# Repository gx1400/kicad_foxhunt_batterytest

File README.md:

# Fox Hunt Controller — Hardware Design

Custom amateur radio fox hunt (hidden transmitter) controller, aimed at being a flexible, dynamic platform for a wide range of fox-hunt formats — not just a fixed single-mode beacon. Built around an ESP32-S3, u-blox GPS module (MAX-M10S), and SA818S 2m RF module, with a WiFi/BLE web UI for configuration and "found" logging, RTOS-based scheduling, RTC-driven wake and precise TX timing, GPS-disciplined timekeeping, and APRS output capability. Firmware developed in PlatformIO. Boards fabricated and assembled via JLCPCB (including their SMT assembly service). Planned as an iterative multi-revision build, proving out core software before locking down hardware.

**Note:** this initial revision is a dev/learning board — built to test out the design, get hands-on with the parts and tooling, and work out mistakes before committing to a more polished revision.

## Contents

- [Setup](#setup)
- [Power architecture overview](#power-architecture-overview) (diagram — full detail in `_docs/`)
- **[Full docs index →](_docs/README.md)** — hardware design detail, controller/peripheral platform decisions, BOM sourcing/datasheets, open items

## Setup

All KiCad design files live under [`pcb/`](pcb/) — project file, schematics, PCB, and the vendored libraries. This project depends on three external symbol/footprint libraries, vendored as git submodules under `pcb/libs/` so the project is self-contained and doesn't require any machine-specific KiCad library setup. Project-level `sym-lib-table` and `fp-lib-table` files reference them via `${KIPRJMOD}`, so they resolve automatically once the submodules are checked out — no manual library registration needed.

Clone with submodules:

```sh
git clone --recurse-submodules https://github.com/gx1400/kicad_foxhunt_batterytest.git
```

The KiCad project file is at `pcb/foxhunt1.kicad_pro`.

Or, if already cloned:

```sh
git submodule update --init --recursive
```

Everything else (standard KiCad libraries: `Device`, `power`, `Resistor_SMD`, etc.) ships with any stock KiCad 10 install — no extra setup required.

## Power Architecture Overview

Two independent power sources feed the board, combined safely before regulation, then split into two independently-regulated rails:

```
18650 pack ──[MAX17320 protector]── +7.5V ──┐
                                              ├─[TPS2121 VCOMP]── VRAW ──[soft-latch FET]──┬─[Buck+LDO]── 5V  (SA818S)
12–14.5V input ──[fuse]── +12V ──────────────┘                                            └─[Buck+LDO]── 3.3V (ESP32-S3, GPS)
```

Full detail (battery protection, dual-input combining, regulation, the whole planned controller/peripheral platform, BOM sourcing, and open items) lives in **[`_docs/`](_docs/README.md)**.

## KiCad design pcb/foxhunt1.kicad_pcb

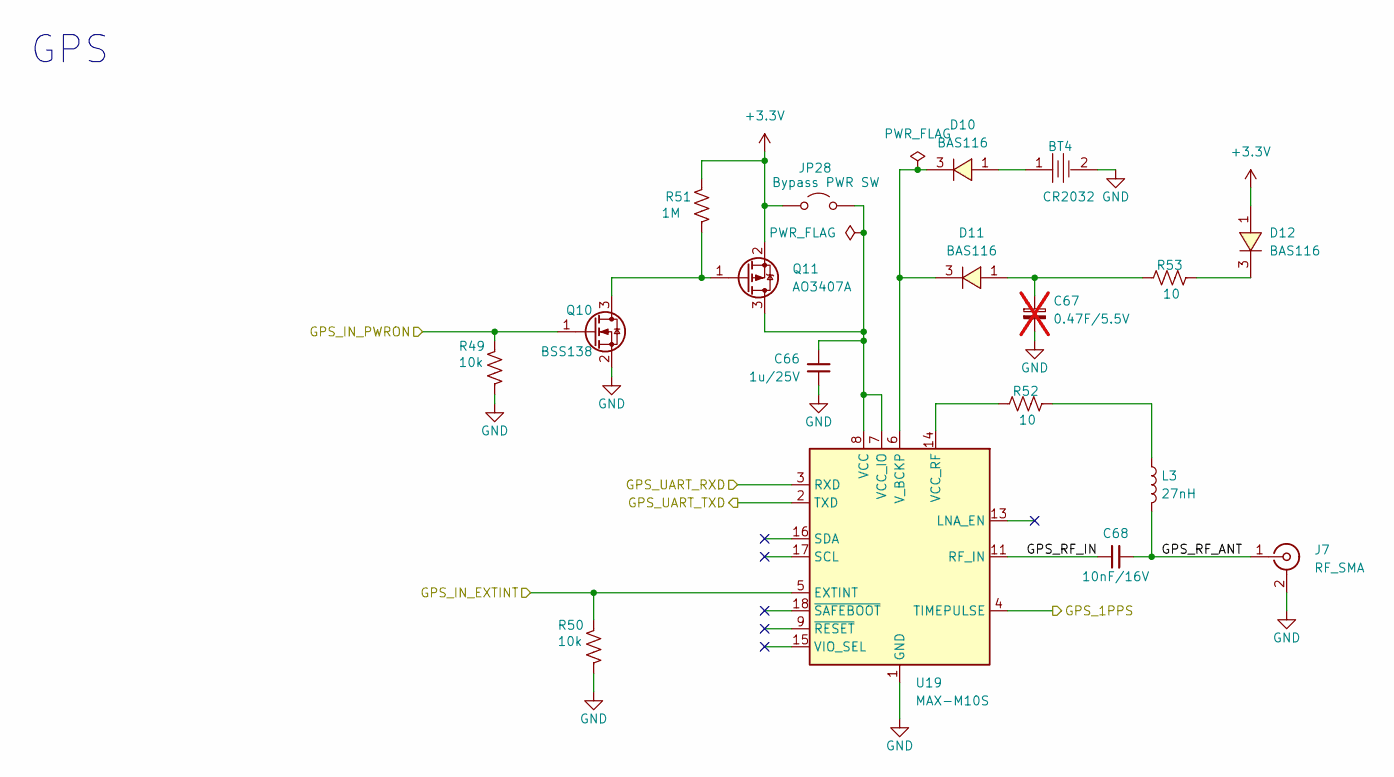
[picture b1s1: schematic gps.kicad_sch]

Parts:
BT4: CR2032; BAT-SMD_BS-08-B2AA016; MPN BS-08-B2AA020-R; LCSC Part C964787
C66: 1u/25V; C_0805_2012Metric; MPN GRM21BR71H105KA12L; LCSC Part # C77083
C67: 0.47F/5.5V; CP_Supercap_EDC474Z5R5V_0.2x5mm; MPN EDC474Z5R5V; LCSC Part # N/A; not fitted
C68: 10nF/16V; C_0603_1608Metric; MPN GRM188R71H103KA01D; LCSC Part # C77053
D10, D11, D12: BAS116; SOT-23_L2.9-W1.3-P1.90-LS2.4-BR; MPN BAS116LT1G; LCSC Part # C232527
J7: RF_SMA; SMA_Amphenol_132134-11_Vertical; MPN 132289; LCSC Part # C3172723
JP28: Bypass PWR SW; TestPoint_2Pads_Pitch2.54mm_Drill0.8mm
L3: 27nH; L_0402_1005Metric; MPN LQG15HS27NG02D; LCSC Part # C3910610
Q10: BSS138; SOT-23
Q11: AO3407A; SOT-23; MPN AO3407A; LCSC Part # C15155
R49, R50: 10k; R_0603_1608Metric; MPN RT0603BRD0710KL; LCSC Part # C95204
R51: 1M; R_0603_1608Metric; MPN RC0603FR-071ML; LCSC Part # C105578
R52: 10; R_1206_3216Metric; MPN RC1206FR-0710RL; LCSC Part # C108080
R53: 10; R_0603_1608Metric; MPN RC0603FR-0710RL; LCSC Part # C109318
U19: MAX-M10S; ublox_MAX; MPN MAX-M10S-00B; LCSC Part # C4153167

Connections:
+3.3V: D12.1, JP28.1 (A), Q11.2 (S), R51.2; also elsewhere on the board
/GPS/GPS_1PPS: U19.4 (TIMEPULSE); also elsewhere on the board
/GPS/GPS_IN_EXTINT: R50.2, U19.5 (EXTINT); also elsewhere on the board
/GPS/GPS_IN_PWRON: Q10.1 (G), R49.2; also elsewhere on the board
/GPS/GPS_RF_ANT: C68.2, J7.1 (In), L3.2
/GPS/GPS_RF_IN: C68.1, U19.11 (RF_IN)
/GPS/GPS_UART_RXD: U19.3 (RXD); also elsewhere on the board
/GPS/GPS_UART_TXD: U19.2 (TXD); also elsewhere on the board
GND: BT4.2, C66.2, C67.2, J7.2 (Ext), Q10.2 (S), R49.1, R50.1, U19.1 (GND), U19.10 (GND), U19.12 (GND); also elsewhere on the board
unnamed: BT4.1, D10.1
unnamed: C67.1, D11.1, R53.2
unnamed: D12.3, R53.1
unnamed: C66.1, JP28.2 (B), Q11.3 (D), U19.7 (VCC_IO), U19.8 (VCC)
unnamed: L3.1, R52.1
unnamed: Q10.3 (D), Q11.1 (G), R51.1
unnamed: R52.2, U19.14 (VCC_RF)
unnamed: D10.3, D11.3, U19.6 (V_BCKP)

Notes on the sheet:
GPS

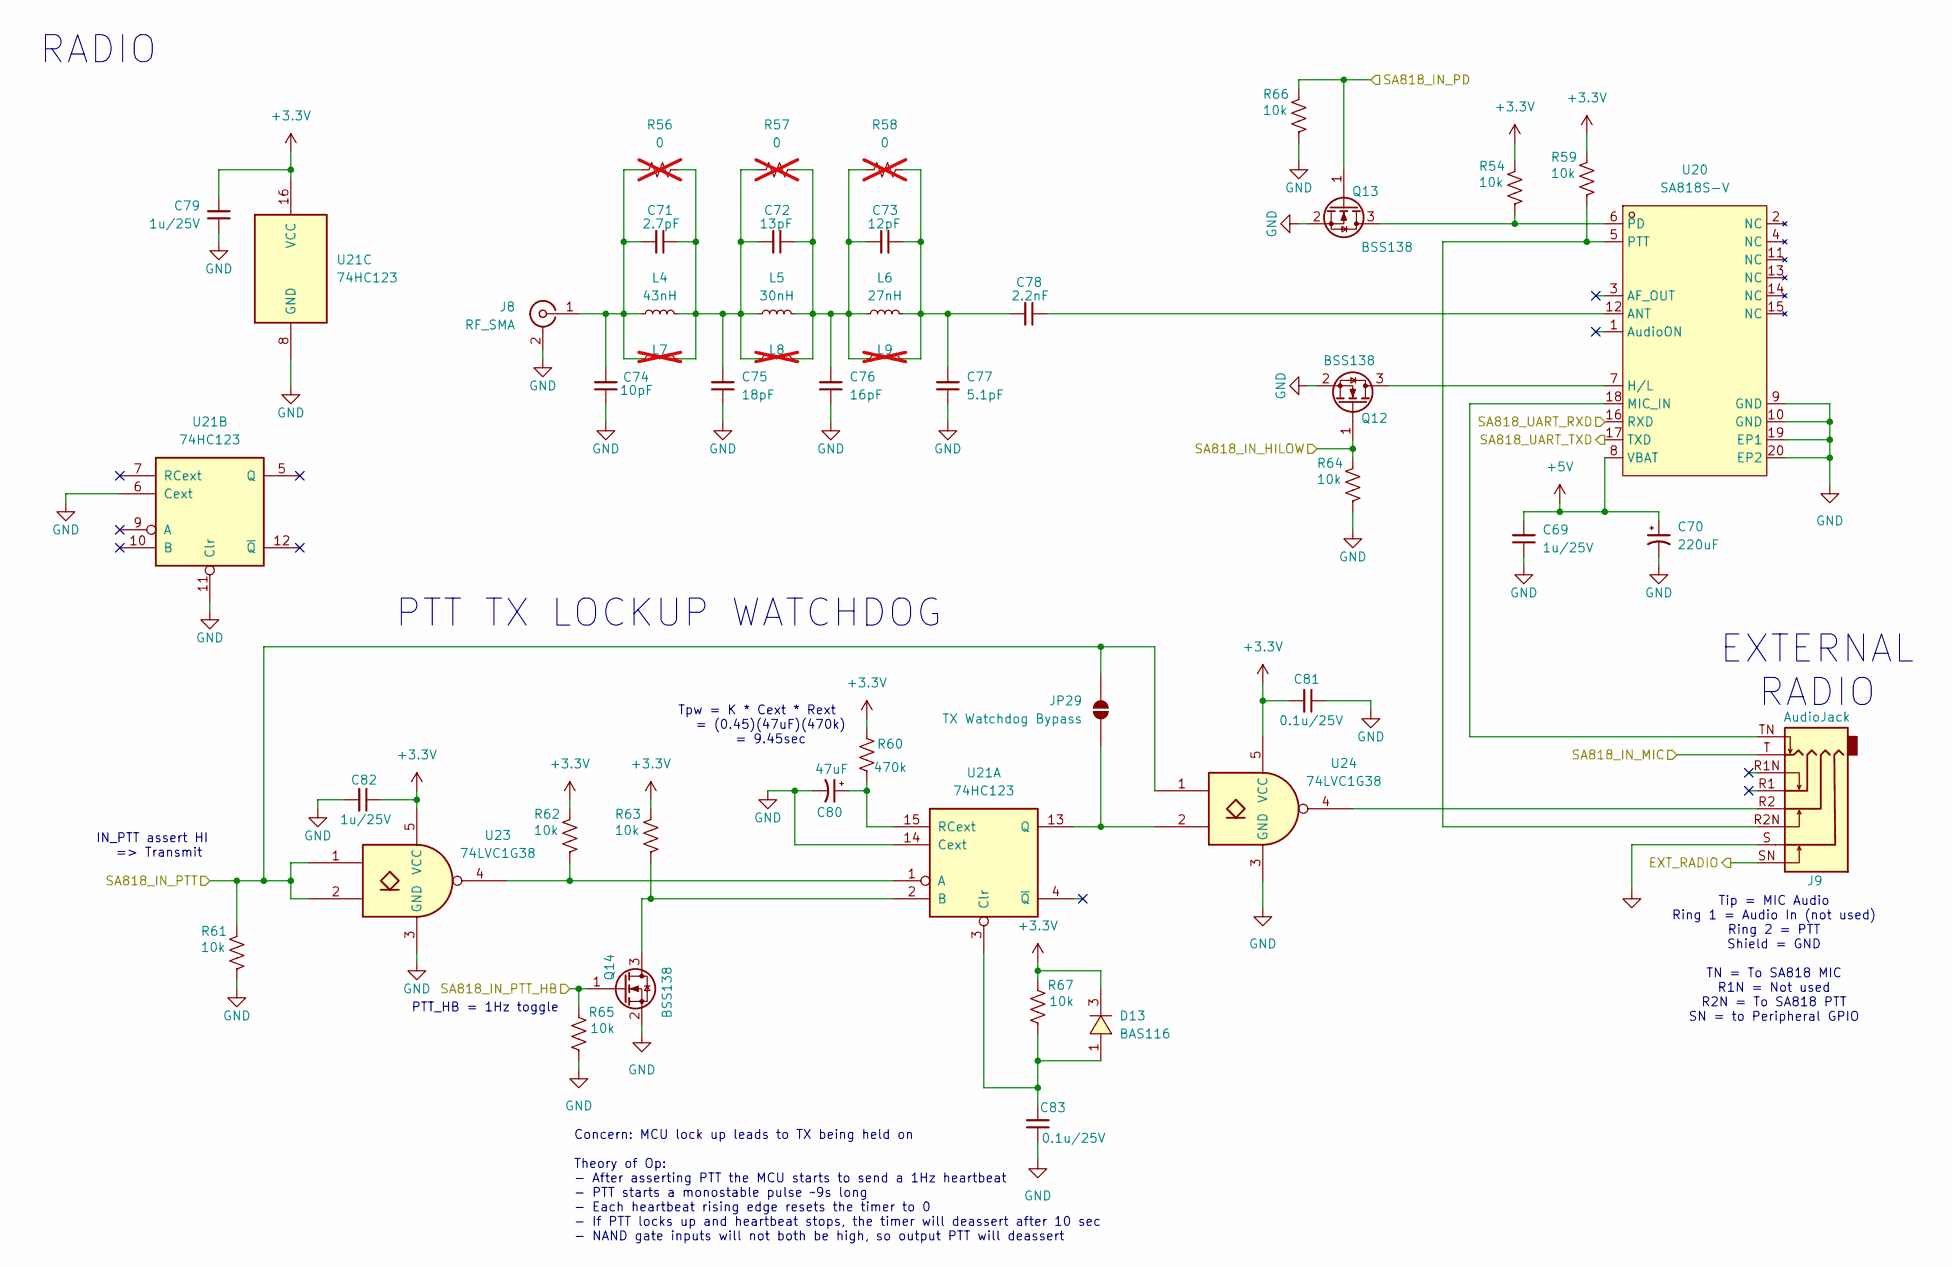
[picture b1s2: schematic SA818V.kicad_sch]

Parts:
C69, C79, C82: 1u/25V; C_0805_2012Metric; MPN GRM21BR71H105KA12L; LCSC Part # C77083
C70: 220uF; CP_Elec_6.3x7.7; MPN DMBJ; LCSC Part # C970695
C71: 2.7pF; C_0603_1608Metric_Pad1.08x0.95mm_HandSolder; MPN GRM1885C1H2R7BA01D; LCSC Part # C162221
C72: 13pF; C_0201_0603Metric_Pad0.64x0.40mm_HandSolder; MPN 0603CG130J500NT; LCSC Part # C34243
C73: 12pF; C_0603_1608Metric_Pad1.08x0.95mm_HandSolder; MPN 0603CG120J500NT; LCSC Part # C1642
C74: 10pF; C_0603_1608Metric_Pad1.08x0.95mm_HandSolder; MPN GRM1885C1H100JA01D; LCSC Part # C84498
C75: 18pF; C_0603_1608Metric_Pad1.08x0.95mm_HandSolder; MPN 0603CG180J500NT; LCSC Part # C92671
C76: 16pF; C_0603_1608Metric_Pad1.08x0.95mm_HandSolder; MPN 0603CG160J500NT; LCSC Part # C1646
C77: 5.1pF; C_0603_1608Metric_Pad1.08x0.95mm_HandSolder; MPN GRM1885C1H5R1CA01D; LCSC Part # C6955114
C78: 2.2nF; C_0603_1608Metric_Pad1.08x0.95mm_HandSolder; MPN GRM1885C1H222JA01J; LCSC Part # C2168957
C80: 47uF; CP-SMD_1206_L3.2-W1.6-FD; MPN TMCMA1A476MTRF; LCSC Part # C4984790
C81, C83: 0.1u/25V; C_0603_1608Metric; MPN GRM188R71H104KA93D; LCSC Part # C77055
D13: BAS116; SOT-23_L2.9-W1.3-P1.90-LS2.4-BR; MPN BAS116LT1G; LCSC Part # C232527
J8: RF_SMA; SMA_Amphenol_132134-11_Vertical; MPN 132289; LCSC Part # C3172723
J9: AudioJack; Jack_SJ-43617-SMT-TR; MPN SJ-43617-SMT-TR; Digikey CP-43617SJTR-ND
JP29: TX Watchdog Bypass; SolderJumper-2_P1.3mm_Open_TrianglePad1.0x1.5mm
L4: 43nH; L_0805_2012Metric_Pad1.05x1.20mm_HandSolder; MPN LQW2BAN43NG00L; LCSC Part # C1330253
L5: 30nH; L_0805_2012Metric_Pad1.05x1.20mm_HandSolder; MPN LQW2BAN30NG00L; LCSC Part # C3221803
L6: 27nH; L_0805_2012Metric_Pad1.05x1.20mm_HandSolder; MPN LQW2BAN27NJ00L; LCSC Part # C1330812
L7, L8, L9: L_0603_1608Metric; not fitted
Q12, Q13, Q14: BSS138; SOT-23
R54, R59, R61, R62, R63, R64, R65, R66, R67: 10k; R_0603_1608Metric; MPN RT0603BRD0710KL; LCSC Part # C95204
R56, R57, R58: 0; R_0603_1608Metric; MPN RC0603JR-070RL; LCSC Part # C95177; not fitted
R60: 470k; R_0603_1608Metric; MPN RC0603FR-07470KL; LCSC Part # C114622
U20: SA818S-V; WIRELM-SMD_G-NICERF_SA818S-X; MPN SA818S-V; LCSC Part C51897911
U21: 74HC123; SOIC-16_3.9x9.9mm_P1.27mm; MPN 74HC123D,653; LCSC Part # C5597
U23, U24: 74LVC1G38; SOT-23-5; MPN SN74LVC1G38DBVR; LCSC Part # C2867613

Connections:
+3.3V: C79.1, C81.1, C82.1, D13.3, R54.2, R59.2, R60.1, R62.2, R63.2, R67.2, U21.16 (VCC), U23.5 (VCC), U24.5 (VCC); also elsewhere on the board
+5V: C69.1, C70.1, U20.8 (VBAT); also elsewhere on the board
/Audio/I2S_MIC_OUT: J9.T; also elsewhere on the board
/Peripherals/PERIPH_OUT_SA818_HILOW: Q12.1 (G), R64.2; also elsewhere on the board
/Peripherals/PERIPH_OUT_SA818_PD: Q13.1 (G), R66.2; also elsewhere on the board
/SA818S-V/EXT_RADIO: J9.SN; also elsewhere on the board
/SA818S-V/SA818_IN_PTT: JP29.2 (B), R61.2, U23.1, U23.2, U24.1; also elsewhere on the board
/SA818S-V/SA818_IN_PTT_HB: Q14.1 (G), R65.2; also elsewhere on the board
/SA818S-V/SA818_UART_RXD: U20.16 (RXD); also elsewhere on the board
/SA818S-V/SA818_UART_TXD: U20.17 (TXD); also elsewhere on the board
GND: C69.2, C70.2, C74.1, C75.1, C76.1, C77.1, C79.2, C80.2, C81.2, C82.2, C83.1, J8.2 (Ext), J9.S, Q12.2 (S), Q13.2 (S), Q14.2 (S), R61.1, R64.1, R65.1, R66.1, U20.9 (GND), U20.10 (GND), U20.19 (EP1), U20.20 (EP2), U21.6 (Cext), U21.8 (GND), U21.11 (Clr), U21.14 (Cext), U23.3 (GND), U24.3 (GND); also elsewhere on the board
unnamed: C71.2, C72.1, C75.2, L4.2, L5.1, L7.2, L8.1, R56.2, R57.1
unnamed: C72.2, C73.1, C76.2, L5.2, L6.1, L8.2, L9.1, R57.2, R58.1
unnamed: C73.2, C77.2, C78.1, L6.2, L9.2, R58.2
unnamed: C71.1, C74.2, J8.1 (In), L4.1, L7.1, R56.1
unnamed: J9.R2, U24.4
unnamed: JP29.1 (A), U21.13 (Q), U24.2
unnamed: Q12.3 (D), U20.7 (H/L)
unnamed: Q13.3 (D), R54.1, U20.6 (PD)
unnamed: Q14.3 (D), R63.1, U21.2 (B)
unnamed: C78.2, U20.12 (ANT)
unnamed: J9.TN, U20.18 (MIC_IN)
unnamed: J9.R2N, R59.1, U20.5 (PTT)
unnamed: R62.1, U21.1 (A), U23.4
unnamed: C83.2, D13.1, R67.1, U21.3 (Clr)
unnamed: C80.1, R60.2, U21.15 (RCext)

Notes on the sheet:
IN_PTT assert HI => Transmit
Tip = MIC Audio Ring 1 = Audio In (not used) Ring 2 = PTT Shield = GND TN = To SA818 MIC R1N = Not used R2N = To SA818 PTT SN = to Peripheral GPIO
EXTERNAL RADIO
Tpw = K * Cext * Rext = (0.45)(47uF)(470k) = 9.45sec
PTT_HB = 1Hz toggle
RADIO
PTT TX LOCKUP WATCHDOG
Concern: MCU lock up leads to TX being held on Theory of Op: - After asserting PTT the MCU starts to send a 1Hz heartbeat - PTT starts a monostable pulse ~9s long - Each heartbeat rising edge resets the timer to 0 - If PTT locks up and heartbeat stops, the timer will deassert after 10 sec - NAND ga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

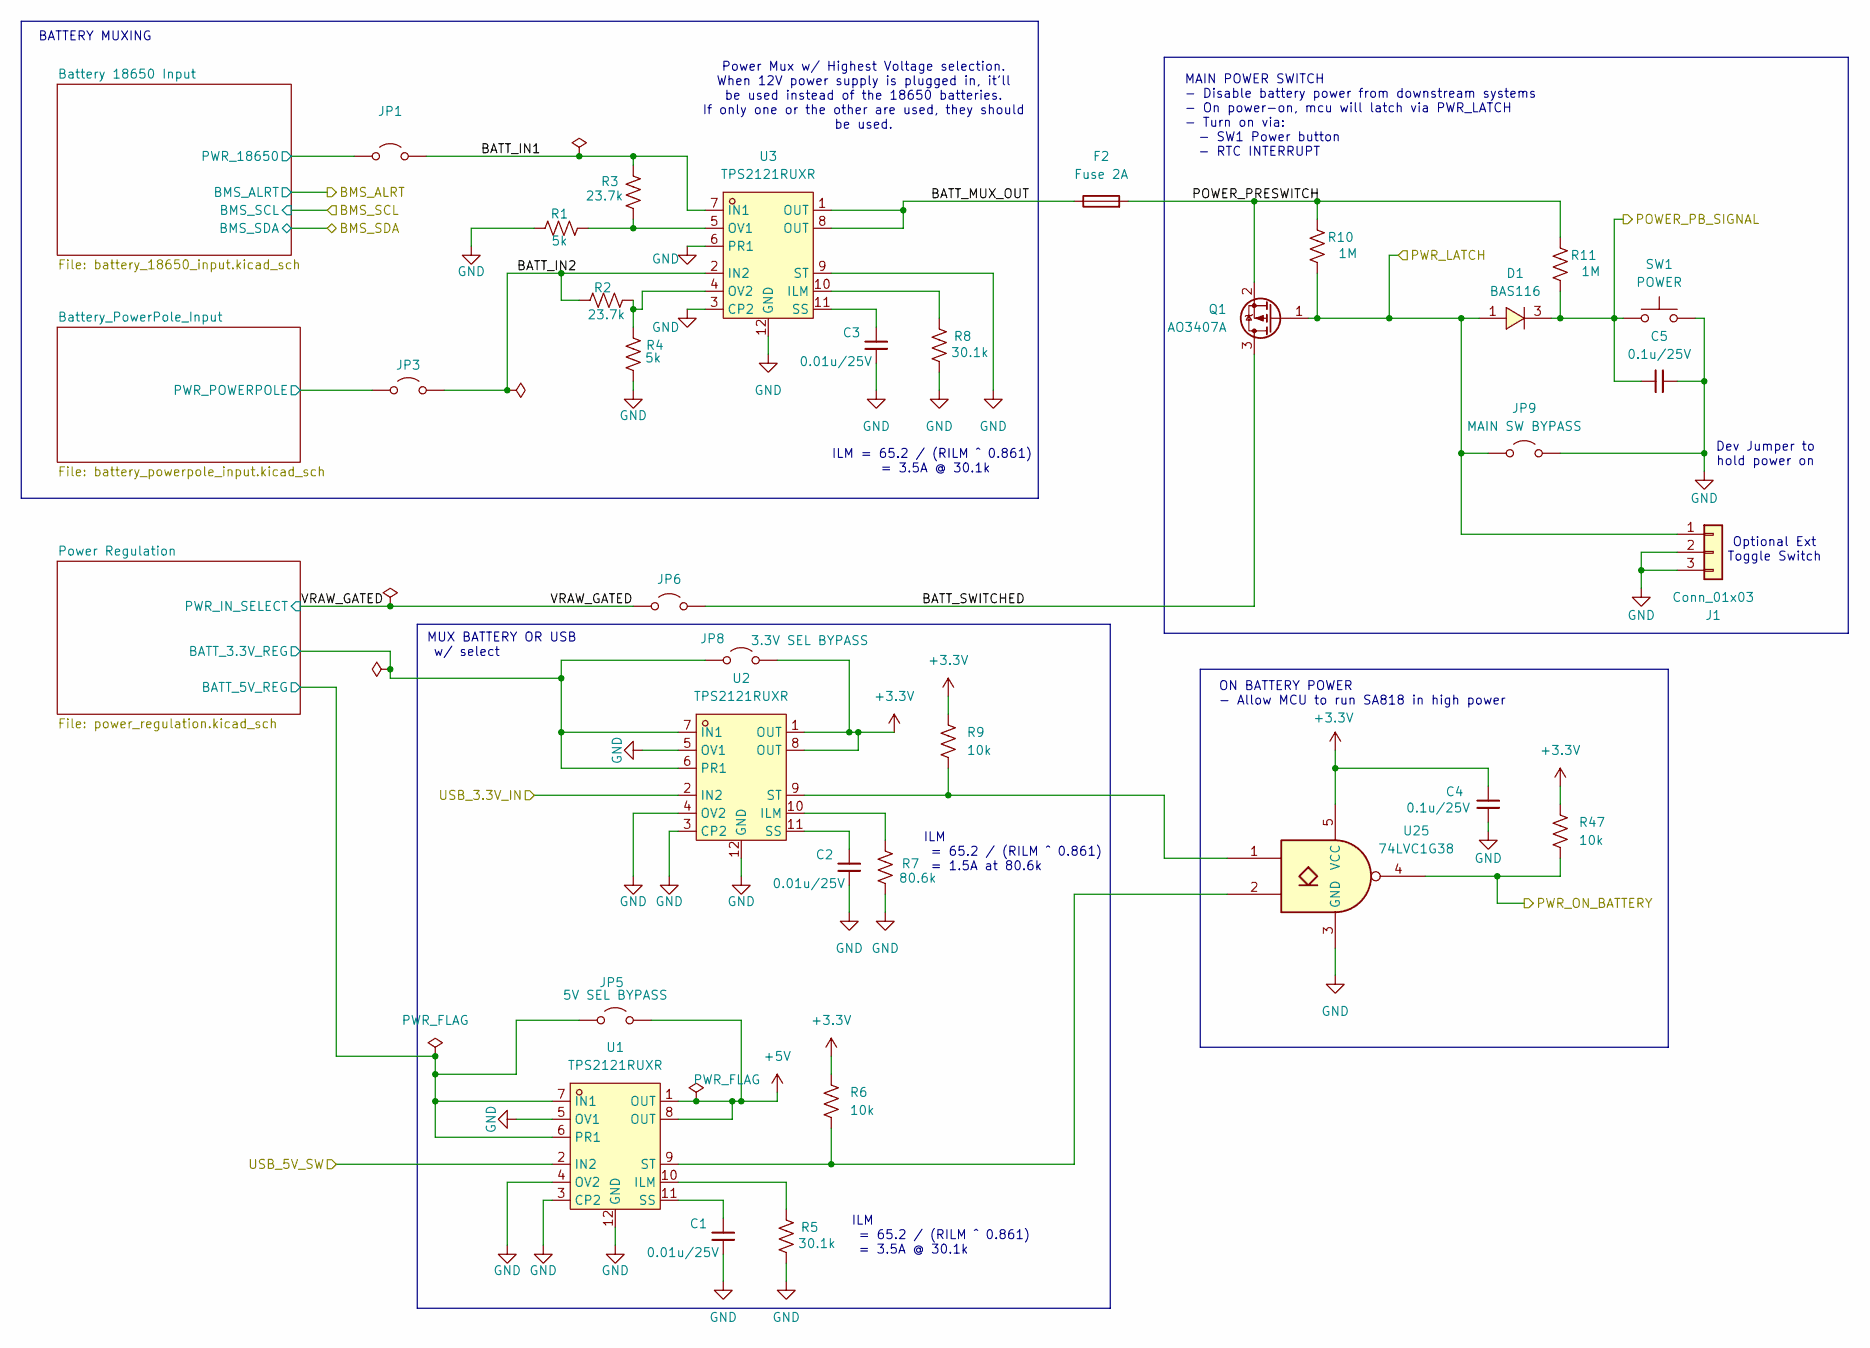
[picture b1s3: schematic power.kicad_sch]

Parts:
C1, C2, C3: 0.01u/25V; C_0603_1608Metric; MPN GRM1885C1H103JA01D; LCSC Part # C85973
C4, C5: 0.1u/25V; C_0603_1608Metric; MPN GRM188R71H104KA93D; LCSC Part # C77055
D1: BAS116; SOT-23_L2.9-W1.3-P1.90-LS2.4-BR; MPN BAS116LT1G; LCSC Part # C232527
F2: Fuse 2A; Fuse_MCCQ-122; MPN MCCQ-122
J1: Conn_01x03; JST_PH_B3B-PH-SM4-TB_1x03-1MP_P2.00mm_Vertical; MPN B3B-PH-SM4-TB(LF)(SN); LCSC Part # C160353
JP1: BATT IN ISO; TestPoint_2Pads_Pitch2.54mm_Drill0.8mm
JP3: 12V IN ISO; TestPoint_2Pads_Pitch2.54mm_Drill0.8mm
JP5: 5V SEL BYPASS; TestPoint_2Pads_Pitch2.54mm_Drill0.8mm
JP6: PWR ISO; TestPoint_2Pads_Pitch2.54mm_Drill0.8mm
JP8: 3.3V SEL BYPASS; TestPoint_2Pads_Pitch2.54mm_Drill0.8mm
JP9: MAIN SW BYPASS; TestPoint_2Pads_Pitch2.54mm_Drill0.8mm
Q1: AO3407A; SOT-23; MPN AO3407A; LCSC Part # C15155
R1, R4: 5k; R_0201_0603Metric; MPN RT0603BRE075KL; LCSC Part # C862232
R2, R3: 23.7k; R_0603_1608Metric; MPN 0603WAF2372T5E; LCSC Part # C22912
R5, R8: 30.1k; R_0603_1608Metric; MPN RC0603FR-0730K1L; LCSC Part # C137745
R6, R9, R47: 10k; R_0603_1608Metric; MPN RT0603BRD0710KL; LCSC Part # C95204
R7: 80.6k; R_0603_1608Metric; MPN RT0603BRE0780K6L; LCSC Part # C862291
R10: 1M; R_0603_1608Metric; MPN RC0603FR-071ML; LCSC Part # C105578
R11: 1M; R_0603_1608Metric; MPN RC0603JR-071ML; LCSC Part # C107698
SW1: POWER; SW_SPST_PTS645Sx43SMTR92; MPN K2-1102SP-A4SC-04; LCSC Part # C83916
U1, U2, U3: TPS2121RUXR; VQFN-HR-12_L2.5-W2.0-P0.50-BL; MPN TPS2121RUXR; LCSC Part # C485916
U25: 74LVC1G38; SOT-23-5; MPN SN74LVC1G38DBVR; LCSC Part # C2867613

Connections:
+3.3V: C4.1, JP8.2 (B), R6.2, R9.2, R47.2, U2.1 (OUT), U2.8 (OUT), U25.5 (VCC); also elsewhere on the board
+5V: JP5.2 (B), U1.1 (OUT), U1.8 (OUT); also elsewhere on the board
/Peripherals/RTC_OUT_INTERRUPT_LATCH: D1.1, J1.1, JP9.1 (A), Q1.1 (G), R10.1; also elsewhere on the board
/Power/BATT_IN1: JP1.2 (B), R3.2, U3.7 (IN1)
/Power/BATT_IN2: JP3.2 (B), R2.2, U3.2 (IN2)
/Power/BATT_MUX_OUT: F2.1, U3.1 (OUT), U3.8 (OUT)
/Power/BATT_SWITCHED: JP6.2 (B), Q1.3 (D)
/Power/Battery 18650 Input/PWR_18650: JP1.1 (A); also elsewhere on the board
/Power/Battery_PowerPole_Input/PWR_POWERPOLE: JP3.1 (A); also elsewhere on the board
/Power/POWER_PB_SIGNAL: C5.1, D1.3, R11.1, SW1.2; also elsewhere on the board
/Power/POWER_PRESWITCH: F2.2, Q1.2 (S), R10.2, R11.2
/Power/PWR_ON_BATTERY: R47.1, U25.4; also elsewhere on the board
/Power/Power Regulation/BATT_3.3V_REG: JP8.1 (A), U2.6 (PR1), U2.7 (IN1); also elsewhere on the board
/Power/Power Regulation/BATT_5V_REG: JP5.1 (A), U1.6 (PR1), U1.7 (IN1); also elsewhere on the board
/Power/USB_3.3V_IN: U2.2 (IN2); also elsewhere on the board
/Power/USB_5V_SW: U1.2 (IN2); also elsewhere on the board
/Power/VRAW_GATED: JP6.1 (A); also elsewhere on the board
GND: C1.2, C2.2, C3.2, C4.2, C5.2, J1.2, J1.3, JP9.2 (B), R1.1, R4.1, R5.1, R7.1, R8.1, SW1.1, U1.3 (CP2), U1.4 (OV2), U1.5 (OV1), U1.12 (GND), U2.3 (CP2), U2.4 (OV2), U2.5 (OV1), U2.12 (GND), U3.3 (CP2), U3.6 (PR1), U3.9 (ST), U3.12 (GND), U25.3 (GND); also elsewhere on the board
unnamed: R5.2, U1.10 (ILM)
unnamed: C1.1, U1.11 (SS)
unnamed: R6.1, U1.9 (ST), U25.2
unnamed: R7.2, U2.10 (ILM)
unnamed: C2.1, U2.11 (SS)
unnamed: R9.1, U2.9 (ST), U25.1
unnamed: R8.2, U3.10 (ILM)
unnamed: R1.2, R3.1, U3.5 (OV1)
unnamed: R2.1, R4.2, U3.4 (OV2)
unnamed: C3.1, U3.11 (SS)

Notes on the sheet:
ILM = 65.2 / (RILM ^ 0.861) = 1.5A at 80.6k
Optional Ext Toggle Switch
Dev Jumper to hold power on
Power Mux w/ Highest Voltage selection. When 12V power supply is plugged in, it'll be used instead of the 18650 batteries. If only one or the other are used, they should be used.
ON BATTERY POWER - Allow MCU to run SA818 in high power
ILM = 65.2 / (RILM ^ 0.861) = 3.5A @ 30.1k
MUX BATTERY OR USB w/ select
ILM = 65.2 / (RILM ^ 0.861) = 3.5A @ 30.1k
BATTERY MUXING
MAIN POWER SWITCH - Disable battery power from downstream systems - On power-on, mcu will latch via PWR_LATCH - Turn on via: - SW1 Power button - RTC INTERRUPT

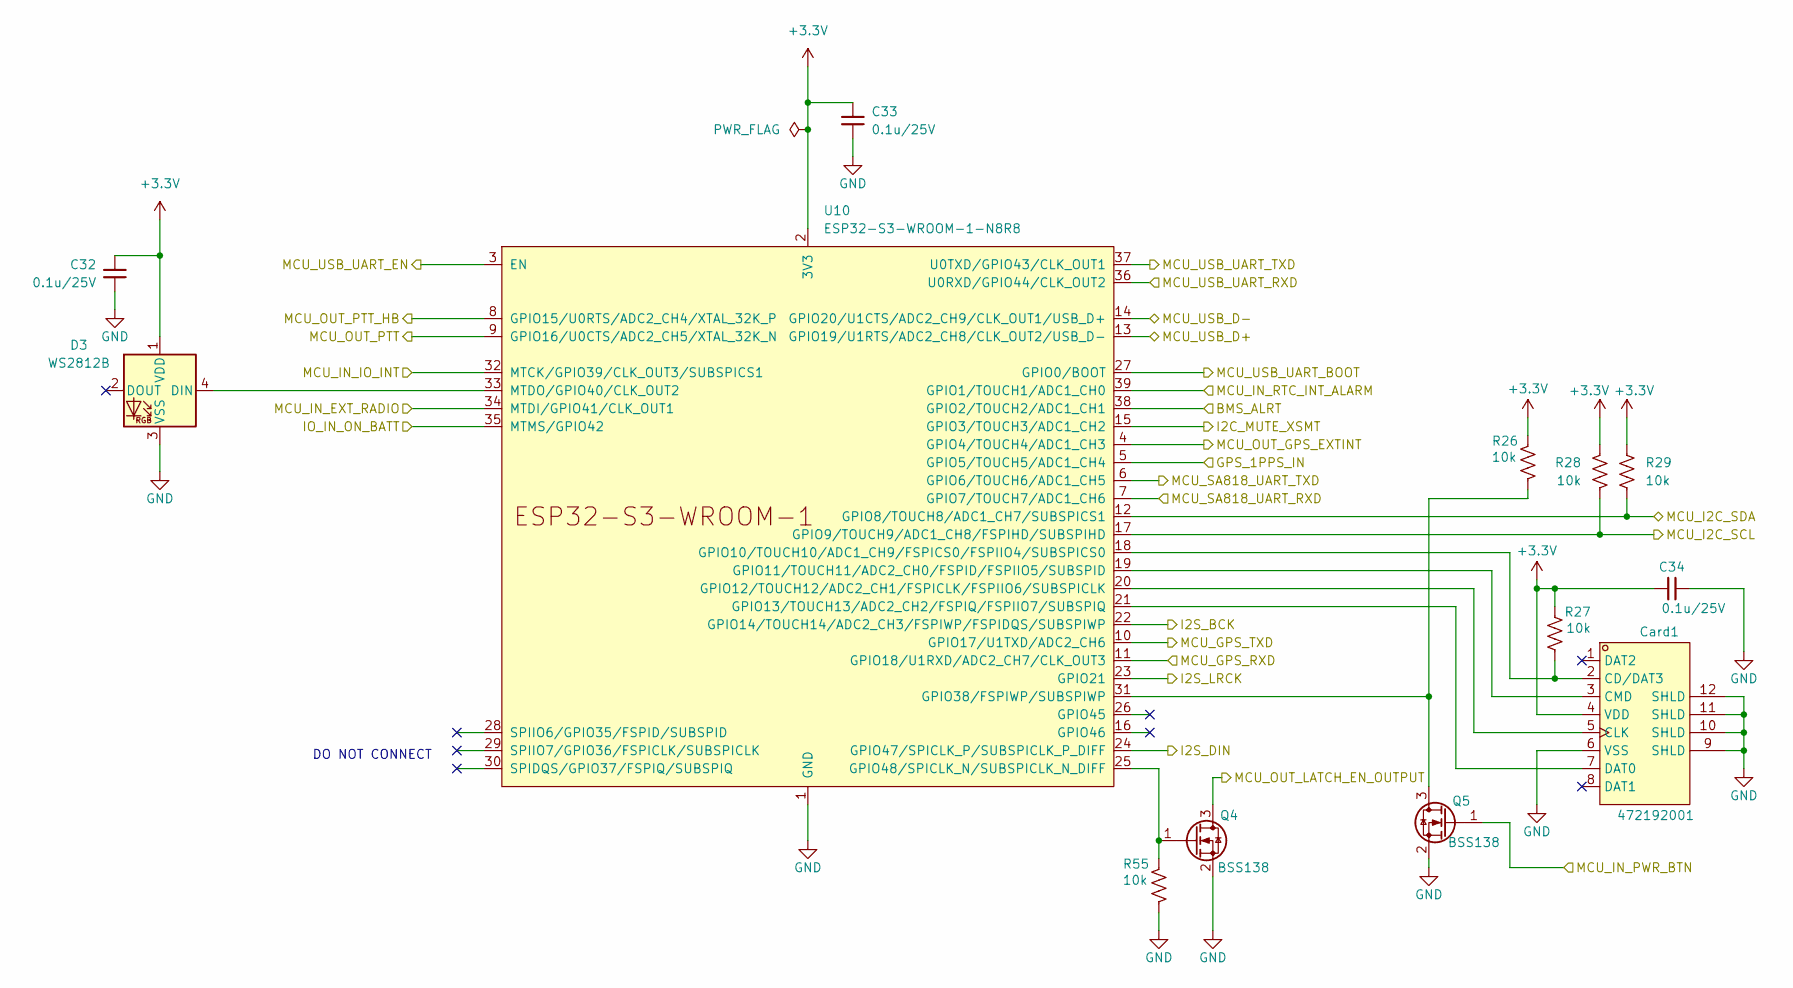
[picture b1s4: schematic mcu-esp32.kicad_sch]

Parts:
C32, C33, C34: 0.1u/25V; C_0603_1608Metric; MPN GRM188R71H104KA93D; LCSC Part # C77055
Card1: 472192001; TF-SMD_472192001; MPN 472192001; LCSC Part # C164170
D3: WS2812B; LED_WS2812B_PLCC4_5.0x5.0mm_P3.2mm; MPN WS2812B-B/W; LCSC Part # C114586
Q4, Q5: BSS138; SOT-23
R26, R27, R28, R29, R55: 10k; R_0603_1608Metric; MPN RT0603BRD0710KL; LCSC Part # C95204
U10: ESP32-S3-WROOM-1-N8R8; ESP32-S3-WROOM-1; MPN ESP32-S3-WROOM-1-N8R8; LCSC Part # C2913201

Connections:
+3.3V: C32.1, C33.1, C34.1, Card1.4 (VDD), D3.1 (VDD), R26.2, R27.2, R28.2, R29.2, U10.2 (3V3); also elsewhere on the board
/Audio/I2S_BCK: U10.22 (GPIO14/TOUCH14/ADC2_CH3/FSPIWP/FSPIDQS/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); also elsewhere on the board
/Audio/I2S_DIN: U10.24 (GPIO47/SPICLK_P/SUBSPICLK_P_DIFF); also elsewhere on the board
/Audio/I2S_LRCK: U10.23 (GPIO21); also elsewhere on the board
/Audio/I2S_XSMT: U10.15 (GPIO3/TOUCH3/ADC1_CH2); also elsewhere on the board
/GPS/GPS_1PPS: U10.5 (GPIO5/TOUCH5/ADC1_CH4); also elsewhere on the board
/GPS/GPS_IN_EXTINT: U10.4 (GPIO4/TOUCH4/ADC1_CH3); also elsewhere on the board
/GPS/GPS_UART_RXD: U10.10 (GPIO17/U1TXD/ADC2_CH6); also elsewhere on the board
/GPS/GPS_UART_TXD: U10.11 (GPIO18/U1RXD/ADC2_CH7/CLK_OUT3); also elsewhere on the board
/Peripherals/PERIPH_IO_INT: U10.32 (MTCK/GPIO39/CLK_OUT3/SUBSPICS1); also elsewhere on the board
/Peripherals/PERIPH_SCL: R28.1, U10.17 (GPIO9/TOUCH9/ADC1_CH8/FSPIHD/SUBSPIHD); also elsewhere on the board
/Peripherals/PERIPH_SDA: R29.1, U10.12 (GPIO8/TOUCH8/ADC1_CH7/SUBSPICS1); also elsewhere on the board
/Peripherals/RTC_OUT_INTERRUPT_LATCH: Q4.3 (D); also elsewhere on the board
/Peripherals/RTC_OUT_MCU_INT_ALRM: U10.39 (GPIO1/TOUCH1/ADC1_CH0); also elsewhere on the board
/Power/BMS_ALRT: U10.38 (GPIO2/TOUCH2/ADC1_CH1); also elsewhere on the board
/Power/POWER_PB_SIGNAL: Q5.1 (G); also elsewhere on the board
/Power/PWR_ON_BATTERY: U10.35 (MTMS/GPIO42); also elsewhere on the board
/SA818S-V/EXT_RADIO: U10.34 (MTDI/GPIO41/CLK_OUT1); also elsewhere on the board
/SA818S-V/SA818_IN_PTT: U10.9 (GPIO16/U0CTS/ADC2_CH5/XTAL_32K_N); also elsewhere on the board
/SA818S-V/SA818_IN_PTT_HB: U10.8 (GPIO15/U0RTS/ADC2_CH4/XTAL_32K_P); also elsewhere on the board
/SA818S-V/SA818_UART_RXD: U10.6 (GPIO6/TOUCH6/ADC1_CH5); also elsewhere on the board
/SA818S-V/SA818_UART_TXD: U10.7 (GPIO7/TOUCH7/ADC1_CH6); also elsewhere on the board
/USB-C/MCU_EN_RESET: U10.3 (EN); also elsewhere on the board
/USB-C/MCU_IO0_BOOT: U10.27 (GPIO0/BOOT); also elsewhere on the board
/USB-C/USB_MCU_D+: U10.13 (GPIO19/U1RTS/ADC2_CH8/CLK_OUT2/USB_D-); also elsewhere on the board
/USB-C/USB_MCU_D-: U10.14 (GPIO20/U1CTS/ADC2_CH9/CLK_OUT1/USB_D+); also elsewhere on the board
/USB-C/USB_UART_RXD: U10.37 (U0TXD/GPIO43/CLK_OUT1); also elsewhere on the board
/USB-C/USB_UART_TXD: U10.36 (U0RXD/GPIO44/CLK_OUT2); also elsewhere on the board
GND: C32.2, C33.2, C34.2, Card1.6 (VSS), Card1.9 (SHLD), Card1.10 (SHLD), Card1.11 (SHLD), Card1.12 (SHLD), D3.3 (VSS), Q4.2 (S), Q5.2 (S), R55.1, U10.1 (GND), U10.40 (GND), U10.41 (GND); also elsewhere on the board
unnamed: Card1.2 (CD/DAT3), R27.1, U10.18 (GPIO10/TOUCH10/ADC1_CH9/FSPICS0/FSPIIO4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)
unnamed: Card1.5 (CLK), U10.20 (GPIO12/TOUCH12/ADC2_CH1/FSPICLK/FSPIIO6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)
unnamed: Card1.3 (CMD), U10.19 (GPIO11/TOUCH11/ADC2_CH0/FSPID/FSPIIO5/S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)
unnamed: Card1.7 (DAT0), U10.21 (GPIO13/TOUCH13/ADC2_CH2/FSPIQ/FSPIIO7/S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)
unnamed: D3.4 (DIN), U10.33 (MTDO/GPIO40/CLK_OUT2)
unnamed: Q4.1 (G), R55.2, U10.25 (GPIO48/SPICLK_N/SUBSPICLK_N_DIFF)
unnamed: Q5.3 (D), R26.1, U10.31 (GPIO38/FSPIWP/SUBSPIWP)

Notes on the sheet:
DO NOT CONNECT

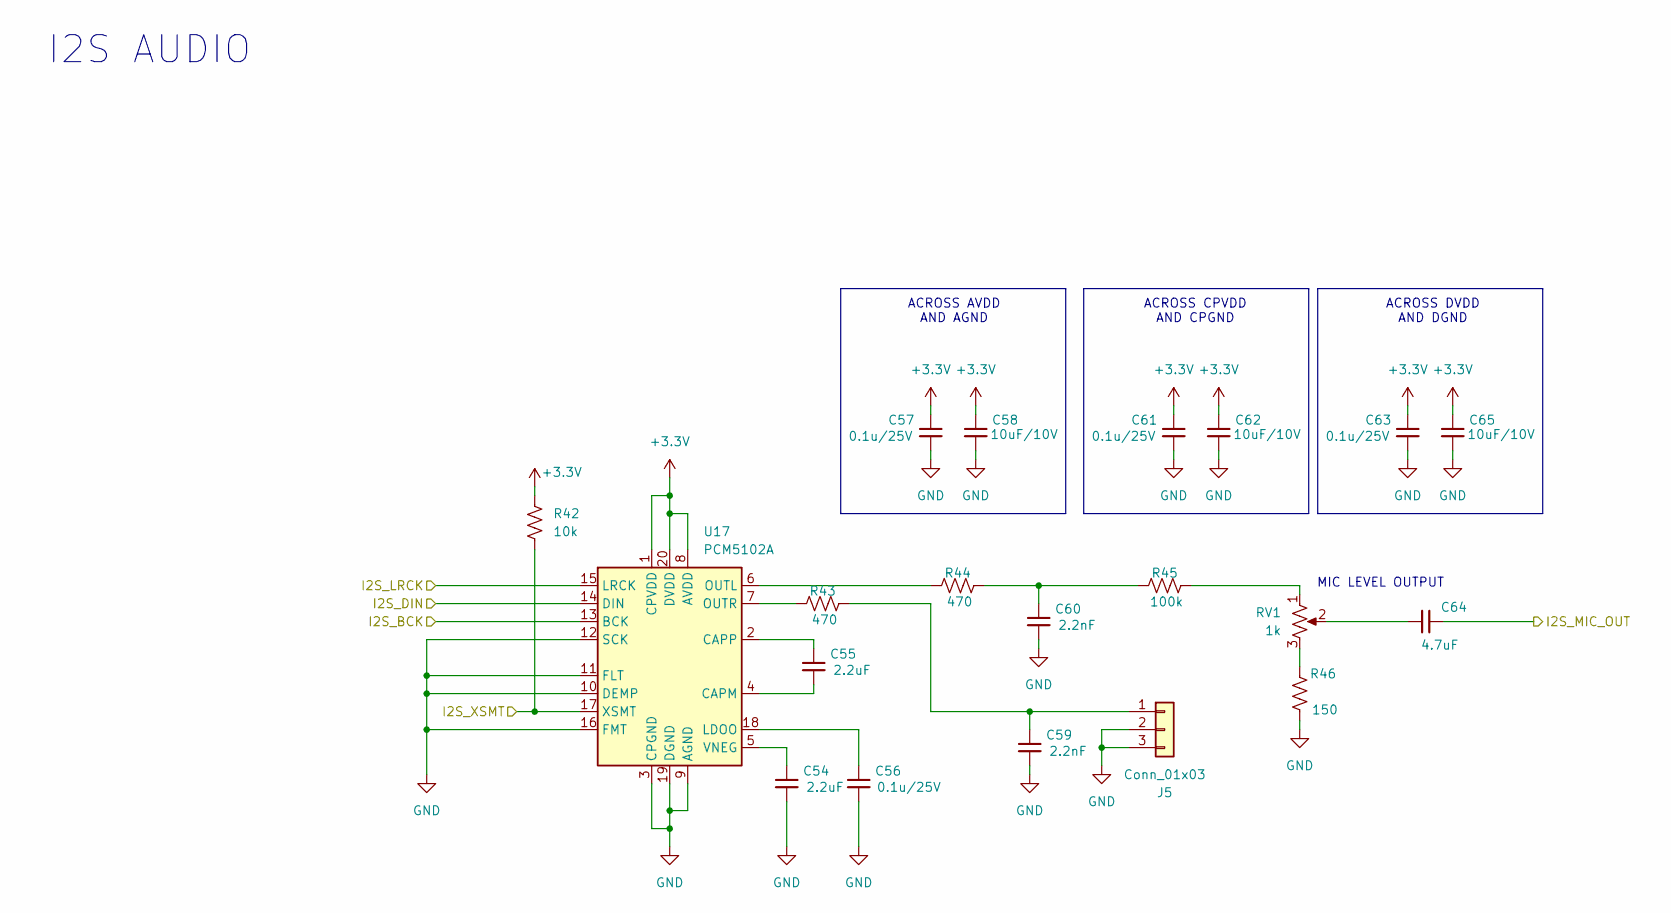
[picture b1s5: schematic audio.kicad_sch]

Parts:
C54, C55: 2.2uF; C_0603_1608Metric; MPN GRM188Z71E225KE43D; LCSC Part # C415535
C56, C57, C61, C63: 0.1u/25V; C_0603_1608Metric; MPN GRM188R71H104KA93D; LCSC Part # C77055
C58, C62, C65: 10uF/10V; C_0603_1608Metric; MPN GRM188Z71A106KA73D; LCSC Part # C2959727
C59, C60: 2.2nF; C_0603_1608Metric; MPN GCM188R71H104KA57D; LCSC Part # C85864
C64: 4.7uF; C_0603_1608Metric; MPN GRM188Z71A475KE15D; LCSC Part # C913474
J5: Conn_01x03; JST_PH_B3B-PH-SM4-TB_1x03-1MP_P2.00mm_Vertical; MPN B3B-PH-SM4-TB(LF)(SN); LCSC Part # C160353
R42: 10k; R_0603_1608Metric; MPN RT0603BRD0710KL; LCSC Part # C95204
R43, R44: 470; R_0603_1608Metric; MPN RT0603BRD07470RL; LCSC Part # C705779
R45: 100k; R_0603_1608Metric; MPN RC0603FR-07100KL; LCSC Part # C14675
R46: 150; R_0603_1608Metric; MPN RC0603JR-07150RL; LCSC Part # C126805
RV1: 1k; Potentiometer_Bourns_3314G_Vertical; MPN 3314G-1-102E; LCSC Part # C780221
U17: PCM5102A; TSSOP-20_4.4x6.5mm_P0.65mm; MPN PCM5102APWR; LCSC Part # C107671

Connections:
+3.3V: C57.1, C58.1, C61.1, C62.1, C63.1, C65.1, R42.2, U17.1 (CPVDD), U17.8 (AVDD), U17.20 (DVDD); also elsewhere on the board
/Audio/I2S_BCK: U17.13 (BCK); also elsewhere on the board
/Audio/I2S_DIN: U17.14 (DIN); also elsewhere on the board
/Audio/I2S_LRCK: U17.15 (LRCK); also elsewhere on the board
/Audio/I2S_MIC_OUT: C64.1; also elsewhere on the board
/Audio/I2S_XSMT: R42.1, U17.17 (XSMT); also elsewhere on the board
GND: C54.2, C56.2, C57.2, C58.2, C59.2, C60.2, C61.2, C62.2, C63.2, C65.2, J5.2, J5.3, R46.1, U17.3 (CPGND), U17.9 (AGND), U17.10 (DEMP), U17.11 (FLT), U17.12 (SCK), U17.16 (FMT), U17.19 (DGND); also elsewhere on the board
unnamed: C60.1, R44.1, R45.2
unnamed: C64.2, RV1.2
unnamed: C59.1, J5.1, R43.1
unnamed: R45.1, RV1.1
unnamed: R46.2, RV1.3
unnamed: C55.2, U17.4 (CAPM)
unnamed: C55.1, U17.2 (CAPP)
unnamed: C56.1, U17.18 (LDOO)
unnamed: R44.2, U17.6 (OUTL)
unnamed: R43.2, U17.7 (OUTR)
unnamed: C54.1, U17.5 (VNEG)

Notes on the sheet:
ACROSS AVDD AND AGND
ACROSS CPVDD AND CPGND
MIC LEVEL OUTPUT
ACROSS DVDD AND DGND
I2S AUDIO
